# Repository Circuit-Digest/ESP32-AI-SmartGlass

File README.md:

# [ESP32-AI-SmartGlass](https://circuitdigest.com/videos/esp32-ai-smartglass)

<br>
The ESP32 AI Smartglass is an innovative wearable device that blends the power of artificial intelligence with the convenience of home automation. Built around the ESP32-S3 mini microcontroller with 4MB of flash and 2MB of PSRAM, this smartglass is equipped to handle a variety of tasks efficiently. With built-in components like the INMP441 microphone, OV2640 camera, and MAX98357 I2S audio amplifier with a speaker, the smart glass is designed for seamless QR code-based control of household appliances. All the hardware is compactly integrated on a single PCB, which also forms the right leg of the smart glass, providing an elegant and functional solution. One of the standout features of the smart glass is its ease of use and versatility. By utilising the camera to scan QR codes, the user can control devices such as lights or fans connected to the same WiFi network. Once powered on, the RGB LEDs provide visual feedback during WiFi connection attempts, and the smart glass offers a welcome chime when the connection is successful. This smart glass removes the need for complex remote controls or hardwired switches, giving users a hands-free, efficient way to manage home automation with a simple glance at the desired QR code.

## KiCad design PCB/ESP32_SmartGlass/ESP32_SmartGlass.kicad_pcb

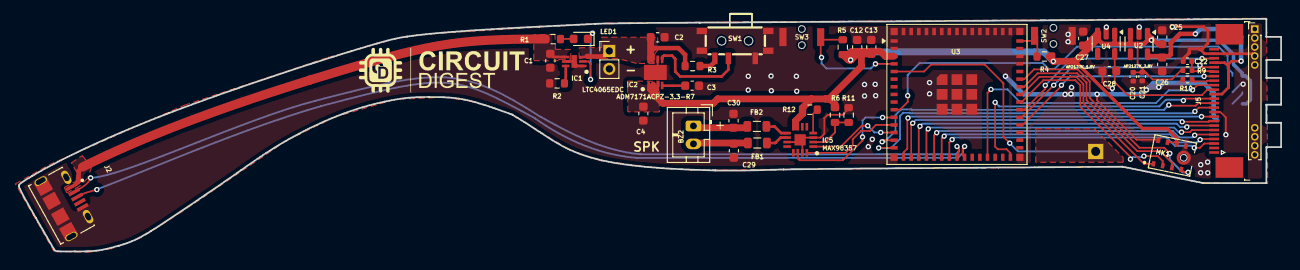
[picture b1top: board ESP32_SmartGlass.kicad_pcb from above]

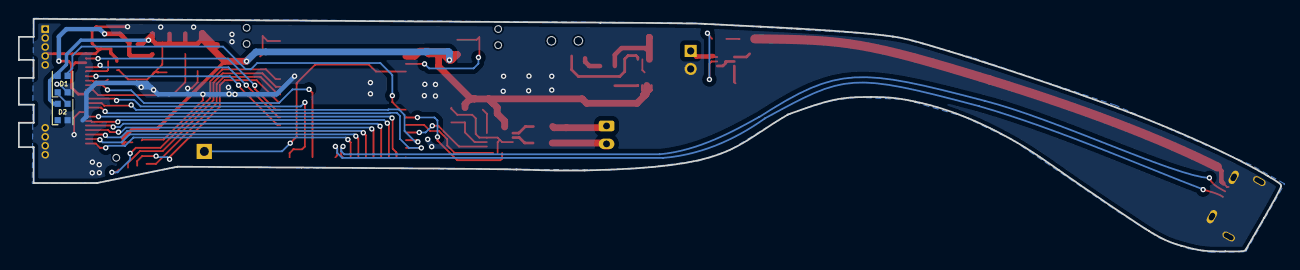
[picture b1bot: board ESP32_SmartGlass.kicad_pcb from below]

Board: 2 copper layers, 140.6 x 25.9 mm, 46 parts (2 on the bottom side), 48 nets.

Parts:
BZ2: SMT-0540-S-R; JST_PH_B2B-PH-K_1x02_P2.00mm_Vertical
C1, C2, C4: 4.7u; C_0603_1608Metric
C3: 1n; C_0603_1608Metric
C12: 2.2uF; C_0603_1608Metric
C13: 100nF; C_0603_1608Metric
C20, C22: 100nf; C_0402_1005Metric
C21: 4.7uf; C_0402_1005Metric
C25, C26, C27, C28, C29, C30: 1u; C_0603_1608Metric
D1, D2: WS2812B-2020; LED_WS2812B-2020_PLCC4_2.0x2.0mm
FB1, FB2: FerriteBead_Small; L_0805_2012Metric
IC1: LTC4065EDC; SON50P200X200X80-7N-D
IC2: ADM7171ACPZ-3.3-R7; SON50P300X300X80-9N-D
IC5: MAX98357AETE+T; QFN50P300X300X80-17N
J1: Conn_01x02; PinHeader_1x02_P2.00mm_Vertical
J2: 10118194-0001LF; AMPHENOL_10118194-0001LF
J3: Conn_01x01; PinHeader_1x01_P2.54mm_Vertical
J5: Conn_01x15; PinHeader_1x15_P1.00mm_Vertical
J5#2: Conn_01x24; TE_2-1734839-4_1x24-1MP_P0.5mm_Horizontal
LED1: Red; LED_0603_1608Metric
MK1: INMP441ACEZ-R7; MIC_INMP441ACEZ-R7
R1: 510; R_0603_1608Metric
R2: 2K; R_0603_1608Metric
R3: 100K; R_0603_1608Metric
R4, R5: 10k; R_0603_1608Metric
R6, R11: NC; R_0603_1608Metric
R9, R10: 10k; R_0402_1005Metric
R12: 0R; R_0603_1608Metric
SW1: K3-1280S-F1; slide switch spdt
SW2: RST; Tactile 3x4x2mm TS-A010
SW3: BOOT; Tactile 3x4x2mm TS-A010
U2: AP2127K-2.8; SOT-23-5
U3: ESP32-S3-MINI-1U; ESP32-S2-MINI-1U
U4: AP2127K-1.8; SOT-23-5

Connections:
+1V8: C28.1, J5#2.10, U4.5 (VOUT)
+2V8: C26.1, J5#2.4, J5#2.11, U2.5 (VOUT)
+3V3: C4.1, C12.2, C13.2, C20.1, C21.1, C25.1, C27.1, D1.4 (VDD), D2.4 (VDD), IC2.1 (VOUT_1), IC2.2 (VOUT_2), IC2.3 (SENSE), IC5.7 (VDD_1), IC5.8 (VDD_2), MK1.7 (VDD), MK1.8 (CHIPEN), R4.1, R5.1, R6.1, R9.1, R12.2, U2.1 (VIN), U2.3 (EN), U3.3 (3V3), U4.1 (VIN), U4.3 (EN)
+BATT: C2.1, IC1.3 (BAT), IC2.7 (VIN_1), IC2.8 (VIN_2), J1.1, R3.1
/LDO_H: R3.2, SW1.3 (C)
D5/I2C_SCL: D1.3 (DIN), U3.10 (IO6)
D6: MK1.3 (WS), U3.39 (TXD0)
D7: MK1.4 (L/R), U3.40 (RXD0)
D8/A8/SCK: IC5.14 (LRCLK), U3.11 (IO7)
D9/A9/MISO: IC5.16 (BCLK), U3.12 (IO8)
D10/A10/MOSI: IC5.1 (DIN), U3.13 (IO9)
EN: R4.2, SW2.2, U3.45 (EN)
GND: C1.2, C2.2, C3.2, C4.2, C12.1, C13.1, C20.2, C21.2, C22.2, C25.2, C26.2, C27.2, C28.2, C29.2, C30.2, D1.2 (VSS), D2.2 (VSS), IC1.1 (GND), IC1.5 (~EN), IC1.7 (EP), IC2.6 (GND), IC2.9 (EP), IC5.3 (GND_1), IC5.11 (GND_2), IC5.15 (GND_3), IC5.17 (THERMAL_PAD), J1.2, J2.5, J2.S1 (SHIELD), J2.S2 (SHIELD__1), J5.1, J5.2, J5.3, J5.4, J5.5, J5.12, J5.13, J5.14, J5.15, J5#2.2, J5#2.15, MK1.5 (GND), MK1.6 (GND__1), MK1.9 (GND__2), R2.2, R10.1, R11.1, SW1.1 (A), SW1.4, SW2.1, SW3.1, U2.2 (GND), U3.1 (GND), U3.2 (GND), U3.42 (GND), U3.43 (GND), U3.46 (GND), U3.47 (GND), U3.48 (GND), U3.49 (GND), U3.50 (GND), U3.51 (GND), U3.52 (GND), U3.53 (GND), U3.54 (GND), U3.55 (GND), U3.56 (GND), U3.57 (GND), U3.58 (GND), U3.59 (GND), U3.60 (GND), U3.61 (GND), U3.62 (GND), U3.63 (GND), U3.64 (GND), U3.65 (GND), U4.2 (GND)
GPIO0: R5.2, SW3.2, U3.4 (IO0)
IO10/XMCLK: J5#2.13, U3.14 (IO10)
IO11/DVP_Y8: J5#2.14, U3.15 (IO11)
IO12/DVP_Y7: J5#2.16, U3.16 (IO12)
IO13/DVP_PCLK: J5#2.17, U3.17 (IO13)
IO14/DVP_YY6: J5#2.18, U3.18 (IO14)
IO15/DVP_Y2: J5#2.19, U3.19 (IO15)
IO16/DVP_Y5: J5#2.20, U3.20 (IO16)
IO17/DVP_Y3: J5#2.21, U3.21 (IO17)
IO18/DVP_Y4: J5#2.22, U3.22 (IO18)
IO38/DVP_VSYNC: J5#2.7, U3.34 (IO38)
IO47/DVP_HREF: J5#2.9, U3.27 (IO47)
IO48/DVP_Y9: J5#2.12, U3.30 (IO48)
MTCK/IO39/CAM_SCL: J5#2.5, U3.35 (IO39)
MTDI/IO41/PDM_DATA: MK1.2 (SD), U3.37 (IO41)
MTDO/IO40/CAMSDA: J5#2.3, U3.36 (IO40)
MTMS/IO42/PDM_CLK: MK1.1 (SCK), U3.38 (IO42)
unnamed: BZ2.1 (+), C30.1, FB2.2
unnamed: BZ2.2 (-), C29.1, FB1.2
unnamed: D1.1 (DOUT), D2.3 (DIN)
unnamed: IC1.6 (PROG), R2.1
unnamed: IC1.2 (~CHRG), LED1.1 (K)
unnamed: C3.1, IC2.4 (SS)
unnamed: IC5.2 (GAIN_SLOT), R6.2, R11.2
unnamed: FB1.1, IC5.10 (OUTN)
unnamed: FB2.1, IC5.9 (OUTP)
unnamed: IC5.4 (~SD_MODE), R12.1
unnamed: J3.1, U3.5 (IO1)
unnamed: C22.1, J5#2.6, R9.2
unnamed: J5#2.8, R10.2
unnamed: LED1.2 (A), R1.2
PWEN: IC2.5 (EN), SW1.2 (B)
USB_D+: J2.3, U3.24 (IO20)
USB_D-: J2.2, U3.23 (IO19)
VBUS: C1.1, IC1.4 (VCC), J2.1, R1.1

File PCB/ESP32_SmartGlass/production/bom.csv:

Designator,Footprint,Quantity,Value,LCSC Part #
BZ2,JST_PH_B2B-PH-K_1x02_P2.00mm_Vertical,1,SMT-0540-S-R,
"C1, C2, C4",0603,3,4.7u,
C12,0603,1,2.2uF,
C13,0603,1,100nF,
"C20, C22",0402,2,100nf,
C21,0402,1,4.7uf,
"C25, C26, C27, C28, C29, C30",0603,6,1u,
C3,0603,1,1n,
"D1, D2",LED_WS2812B-2020_PLCC4_2.0x2.0mm,2,WS2812B-2020,
"FB1, FB2",0805,2,FerriteBead_Small,
IC1,SON50P200X200X80-7N-D,1,LTC4065EDC,
IC2,SON50P300X300X80-9N-D,1,ADM7171ACPZ-3.3-R7,
IC5,QFN50P300X300X80-17N,1,MAX98357AETE+T,
J1,PinHeader_1x02_P2.00mm_Vertical,1,Conn_01x02,
J2,AMPHENOL_10118194-0001LF,1,10118194-0001LF,
J3,PinHeader_1x01_P2.54mm_Vertical,1,Conn_01x01,
J5_2,PinHeader_1x15_P1.00mm_Vertical,1,Conn_01x15,
J5,TE_2-1734839-4_1x24-1MP_P0.5mm_Horizontal,1,Conn_01x24,
LED1,0603,1,Red,
MK1,MIC_INMP441ACEZ-R7,1,INMP441ACEZ-R7,
R1,0603,1,510,
"R10, R9",0402,2,10k,
"R11, R6",0603,2,NC,
R12,0603,1,0R,
R2,0603,1,2K,
R3,0603,1,100K,
"R4, R5",0603,2,10k,
SW1,slide switch spdt,1,K3-1280S-F1 ,
SW2,Tactile 3x4x2mm TS-A010,1,RST,
SW3,Tactile 3x4x2mm TS-A010,1,BOOT,
U2,SOT-23-5,1,AP2127K-2.8,
U3,ESP32-S2-MINI-1U,1,ESP32-S3-MINI-1U,
U4,SOT-23-5,1,AP2127K-1.8,
